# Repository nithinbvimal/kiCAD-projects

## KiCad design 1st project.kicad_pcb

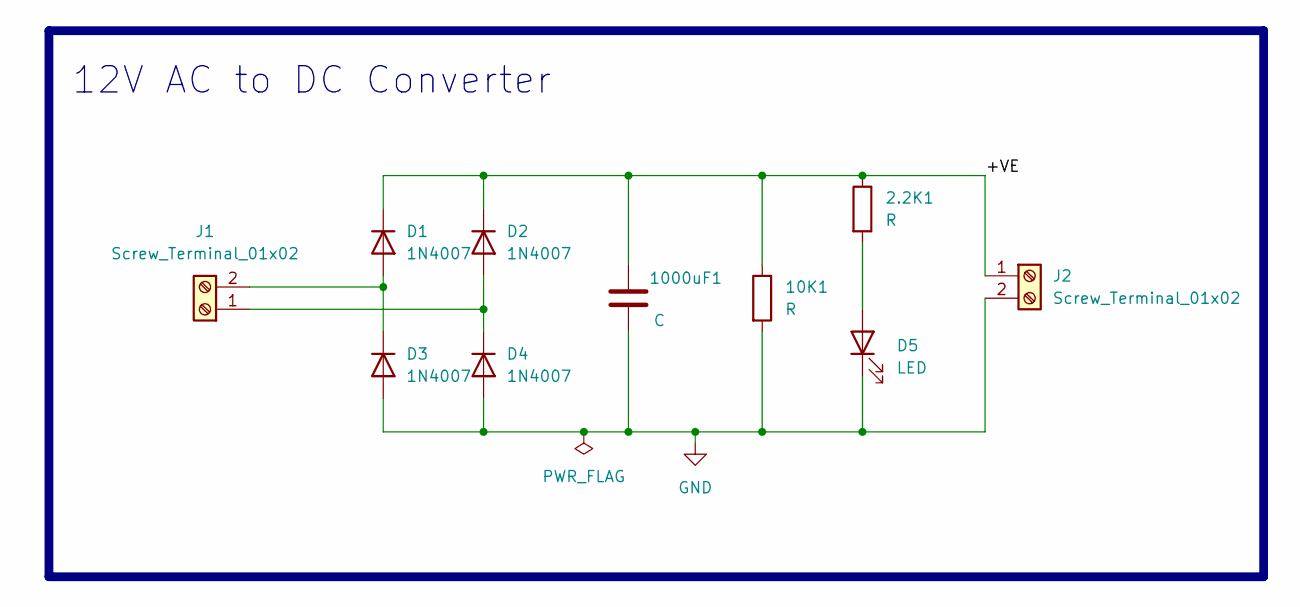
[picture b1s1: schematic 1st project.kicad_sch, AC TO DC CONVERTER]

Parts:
2.2K1, 10K1: R; R_Axial_DIN0204_L3.6mm_D1.6mm_P7.62mm_Horizontal
1000uF1: C; C_Radial_D8.0mm_H7.0mm_P3.50mm
D1, D2, D3, D4: 1N4007; D_DO-41_SOD81_P10.16mm_Horizontal
D5: LED; LED_D5.0mm_Horizontal_O1.27mm_Z3.0mm
J1, J2: Screw_Terminal_01x02; TerminalBlock_bornier-2_P5.08mm

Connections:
/+VE: 2.2K1.1, 10K1.1, 1000uF1.1, D1.1 (K), D2.1 (K), J2.1
GND: 10K1.2, 1000uF1.2, D3.2 (A), D4.2 (A), D5.1 (K), J2.2
unnamed: D1.2 (A), D3.1 (K), J1.2
unnamed: D2.2 (A), D4.1 (K), J1.1
unnamed: 2.2K1.2, D5.2 (A)

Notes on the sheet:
12V AC to DC Converter

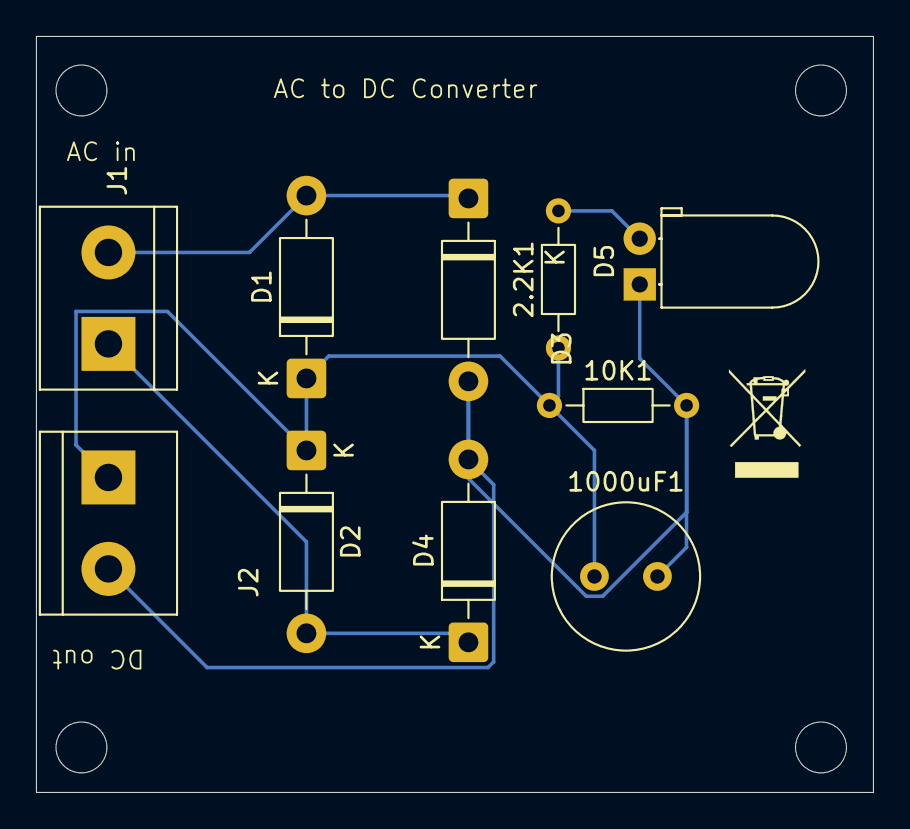
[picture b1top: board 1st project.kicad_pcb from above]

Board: 2 copper layers, 46.5 x 42.0 mm, 10 parts (0 on the bottom side), 5 nets.

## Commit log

2025-07-12 Create README.md
    This is my first kiCAD project(PCB designing) based on 12V AC to DC converter
2025-07-12 Add files via upload
    Added the project files
